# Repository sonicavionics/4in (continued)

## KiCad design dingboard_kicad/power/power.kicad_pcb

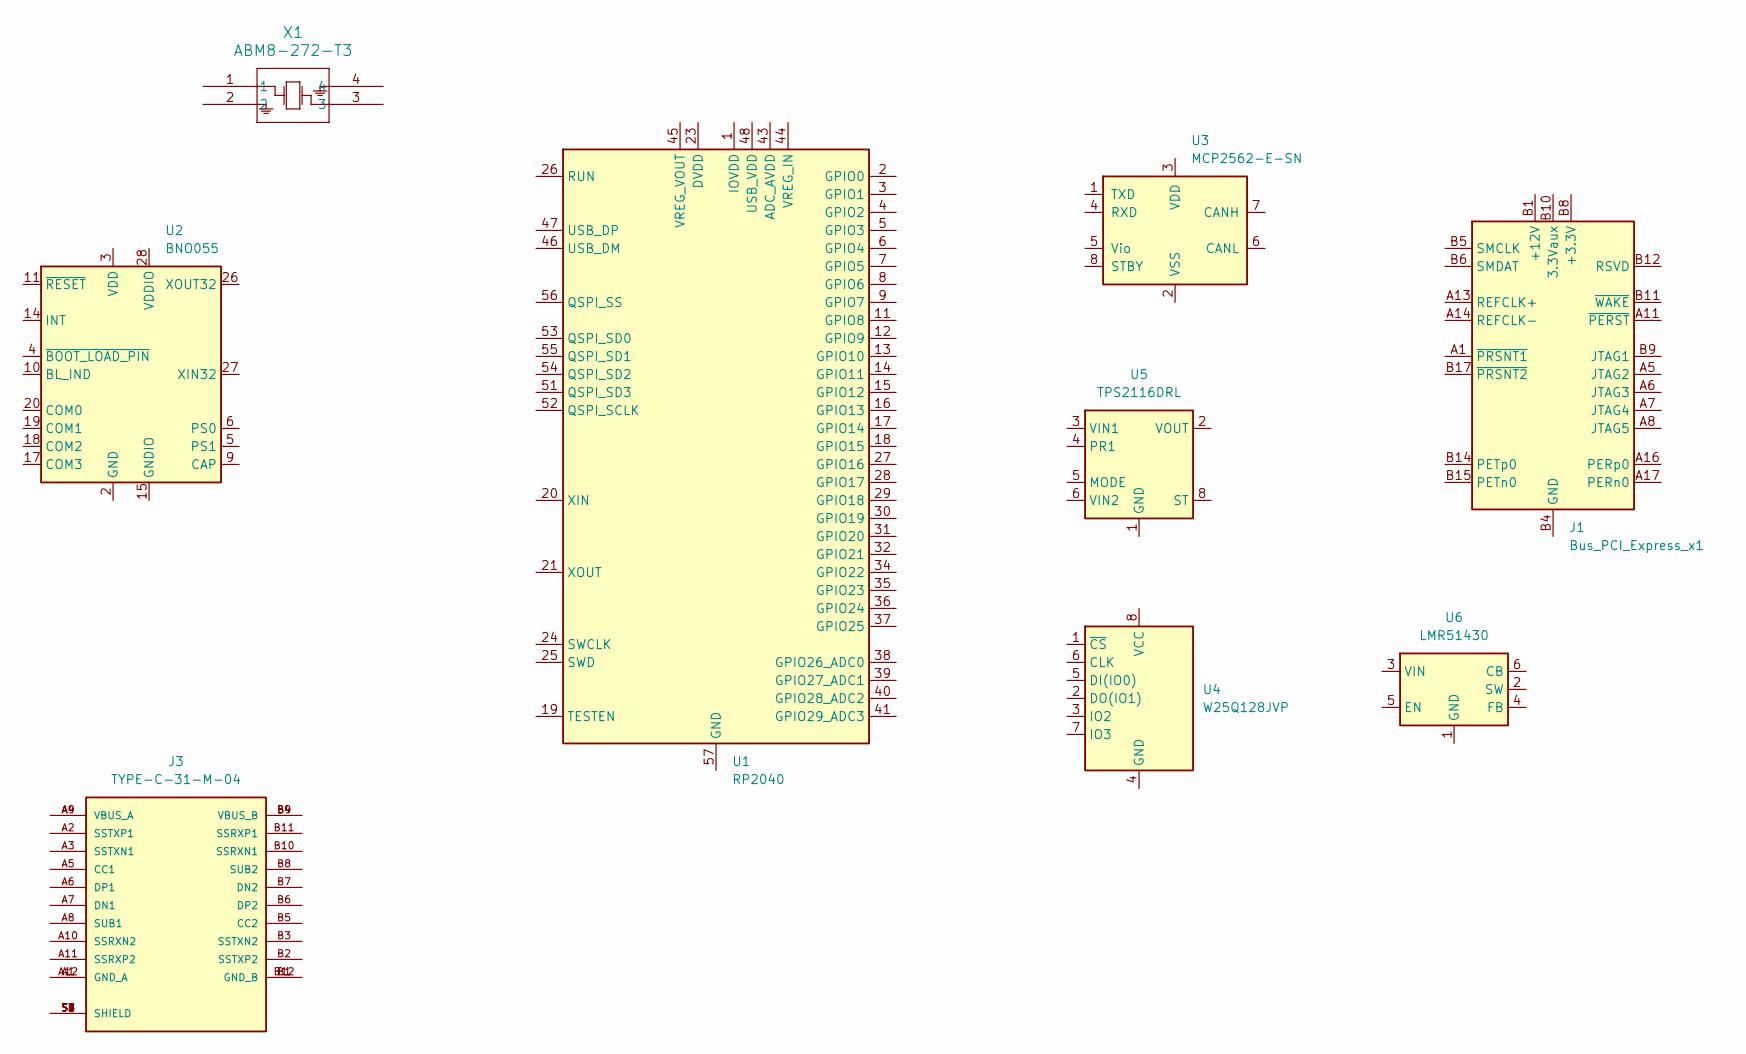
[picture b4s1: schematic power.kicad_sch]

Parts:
J1: Bus_PCI_Express_x1; BUS_PCIexpress_x1; LCSC n/a
J3: TYPE-C-31-M-04; HRO_TYPE-C-31-M-04; PARTREV A; LCSC C129018
U1: RP2040; QFN-56-1EP_7x7mm_P0.4mm_EP3.2x3.2mm; LCSC C2040
U2: BNO055; LGA-28_5.2x3.8mm_P0.5mm; LCSC C93216
U3: MCP2562-E-SN; SOIC-8_3.9x4.9mm_P1.27mm
U4: W25Q128JVP; WSON-8-1EP_6x5mm_P1.27mm_EP3.4x4.3mm; LCSC C190862
U5: TPS2116DRL; SOT-583-8
U6: LMR51430; SOT-23-6
X1: ABM8-272-T3; ABM8-272-T3_ABR

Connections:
unnamed: J1.A9 (+3.3V), J1.A10 (+3.3V), J1.B8 (+3.3V)
unnamed: J1.A2 (+12V), J1.A3 (+12V), J1.B1 (+12V), J1.B2 (+12V), J1.B3 (+12V)
unnamed: J1.A4 (GND), J1.A12 (GND), J1.A15 (GND), J1.A18 (GND), J1.B4 (GND), J1.B7 (GND), J1.B13 (GND), J1.B16 (GND), J1.B18 (GND)
unnamed: J3.A1 (GND_A), J3.A12 (GND_A)
unnamed: J3.B1 (GND_B), J3.B12 (GND_B)
unnamed: J3.S1 (SHIELD), J3.S2 (SHIELD), J3.S3 (SHIELD), J3.S4 (SHIELD), J3.S5 (SHIELD), J3.S6 (SHIELD), J3.S7 (SHIELD), J3.S8 (SHIELD)
unnamed: J3.A4 (VBUS_A), J3.A9 (VBUS_A)
unnamed: J3.B4 (VBUS_B), J3.B9 (VBUS_B)
unnamed: U1.23 (DVDD), U1.50 (DVDD)
unnamed: U1.1 (IOVDD), U1.10 (IOVDD), U1.22 (IOVDD), U1.33 (IOVDD), U1.42 (IOVDD), U1.49 (IOVDD)
unnamed: U2.15 (GNDIO), U2.16 (GNDIO), U2.25 (GNDIO)
unnamed: U5.2 (VOUT), U5.7 (VOUT)

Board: 2 copper layers, 9 parts (0 on the bottom side), 12 nets, no tracks yet.

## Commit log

2024-11-16 init
2024-11-16 Stop tracking files in .gitignore
2024-11-17 rename
2024-11-17 add RT9080-33GJ5
2024-11-17 begin adding chips
2024-11-17 add more files
2024-11-17 add rp2040 library
2024-11-17 add more rp2040 libary
2024-11-18 nov 17 save
2024-11-19 begin protection ic schematic
2024-11-20 complete battery protection IC
2024-11-20 refactor folders
2024-11-20 auto annotate
2024-11-20 test
2024-11-21 update BOM
2024-11-21 finish charger/switching IC
2024-11-21 finish buck boost
2024-11-21 add fuel guage
2024-11-21 start PCB layout
2024-11-21 sync
2024-11-22 refactor fuel guage
2024-11-22 add design rules from JLC
2024-11-22 refactor charger/switch
2024-11-22 change all components to 0402 from 0603
2024-11-25 route switching/charging ic
2024-11-25 route battery protection ic
2024-11-26 add gold fingers
2024-12-01 reclaim project from altium 365
2024-12-01 save outjob files
2024-12-02 generate fab files
2024-12-02 fix LED polarity, add top silkscreen to clairify pin 1 on all ICs, add back missing via, update version number.
2024-12-02 add spacing to vias
2024-12-04 add solidworks files, update outjob file
2024-12-04 init new CAD files
2024-12-04 begin assembly for avionics bay
2024-12-04 init backplate assembly
2024-12-04 set variables to dynamically update card number
2024-12-05 finish first revision of avionics bay
2024-12-06 swtich to circular design to fit the RFD 900
2024-12-06 complete finish new avionics template
2024-12-08 finalize avionics bay design
2024-12-08 clean up
2024-12-08 output dxf files for ECAD
2024-12-09 init kicad
2024-12-09 sync solidworks
2024-12-09 update DXF files
2024-12-09 add reference step file from kicad PCIe
2024-12-09 update PCIe port to match KiCad footprint
2024-12-09 update DXF files from solidworks
2024-12-09 add components to kicad power module
2024-12-09 revert back pcie to right side short
2024-12-09 add backplate dxf file
2024-12-09 create kicad template
2024-12-12 place BME680 in dingboard sensors schematic
2024-12-13 update BOM with new chip list
2024-12-15 update BNO055 schematic
2024-12-15 add 5v buck-boost for CAN chip
2024-12-15 export pdf of schematic
2024-12-17 remove mux over volt protection
2024-12-18 add current estimation to BOM
2024-12-18 update gitignore to include kicad files
2024-12-23 switch to Sonic Avionics
2024-12-23 update capacitors for basic assembly, export new schematic PDF
2024-12-24 remove dingboard from names
2024-12-24 add .lck files to .gitignore
2024-12-24 add kicad footprint library submodule
2024-12-24 move template to modules folder
2024-12-24 update submodule
2024-12-24 add all project specific footprints
2024-12-24 update symbol library to use project specific library
2024-12-26 add no connect to USB power pins
2024-12-26 reassign PCIe pins
2024-12-26 fix voltage labels
2024-12-26 add momentary buttons to schematic
2024-12-26 begin routing
2024-12-26 continue routing
2024-12-27 finish most routing
2024-12-28 add new sensors, LDO and MOSFET
2024-12-28 finish initial routing
2024-12-29 change USB-C connector
2024-12-30 mod ground planes
2024-12-30 route under rp2040
2024-12-30 complete all routing connections, and planes
2024-12-31 refine routing
2024-12-31 update backplate libraries and schematic
2024-12-31 update PCIe footprint; delete holes, and pads
2025-01-01 finish diff pairs and planes
2025-01-01 Sensors (#4)
    * delete regs and mux
    * add no connect to USB power pins
    * reassign PCIe pins
    * fix voltage labels
    * add momentary buttons to schematic
    * begin routing
2025-01-01 Sensors (#5)
    * delete regs and mux
    * add no connect to USB power pins
    * reassign PCIe pins
    * fix voltage labels
    * add momentary buttons to schematic
    * begin routing
2025-01-01 update PCIe nets
2025-01-01 backplate: update PCIe pins
2025-01-01 sensors: update PCIe pin nets, refine routing
2025-01-02 backplate: finish initial revision
2025-01-02 init powersim module
2025-01-02 powersim: add all components to schematic
2025-01-02 sensors: update BOM
2025-01-02 powersim: resize schematic page
2025-01-02 powersim: finish PCB
2025-01-02 powersim: finish board
2025-01-02 Create LICENSE
2025-01-03 sensors: generate final production files
2025-01-03 backplate: generate final production files
2025-01-03 powersim: generate final production files
2025-01-03 Revert kicad/modules/backplate/backplate.kicad_prl to aa3ca6f3f7ed60b4904834a44ccae3b66bebb62d
2025-01-03 revise production files
2025-01-03 revise production files again
2025-01-03 sensors: update vias under rp2040
